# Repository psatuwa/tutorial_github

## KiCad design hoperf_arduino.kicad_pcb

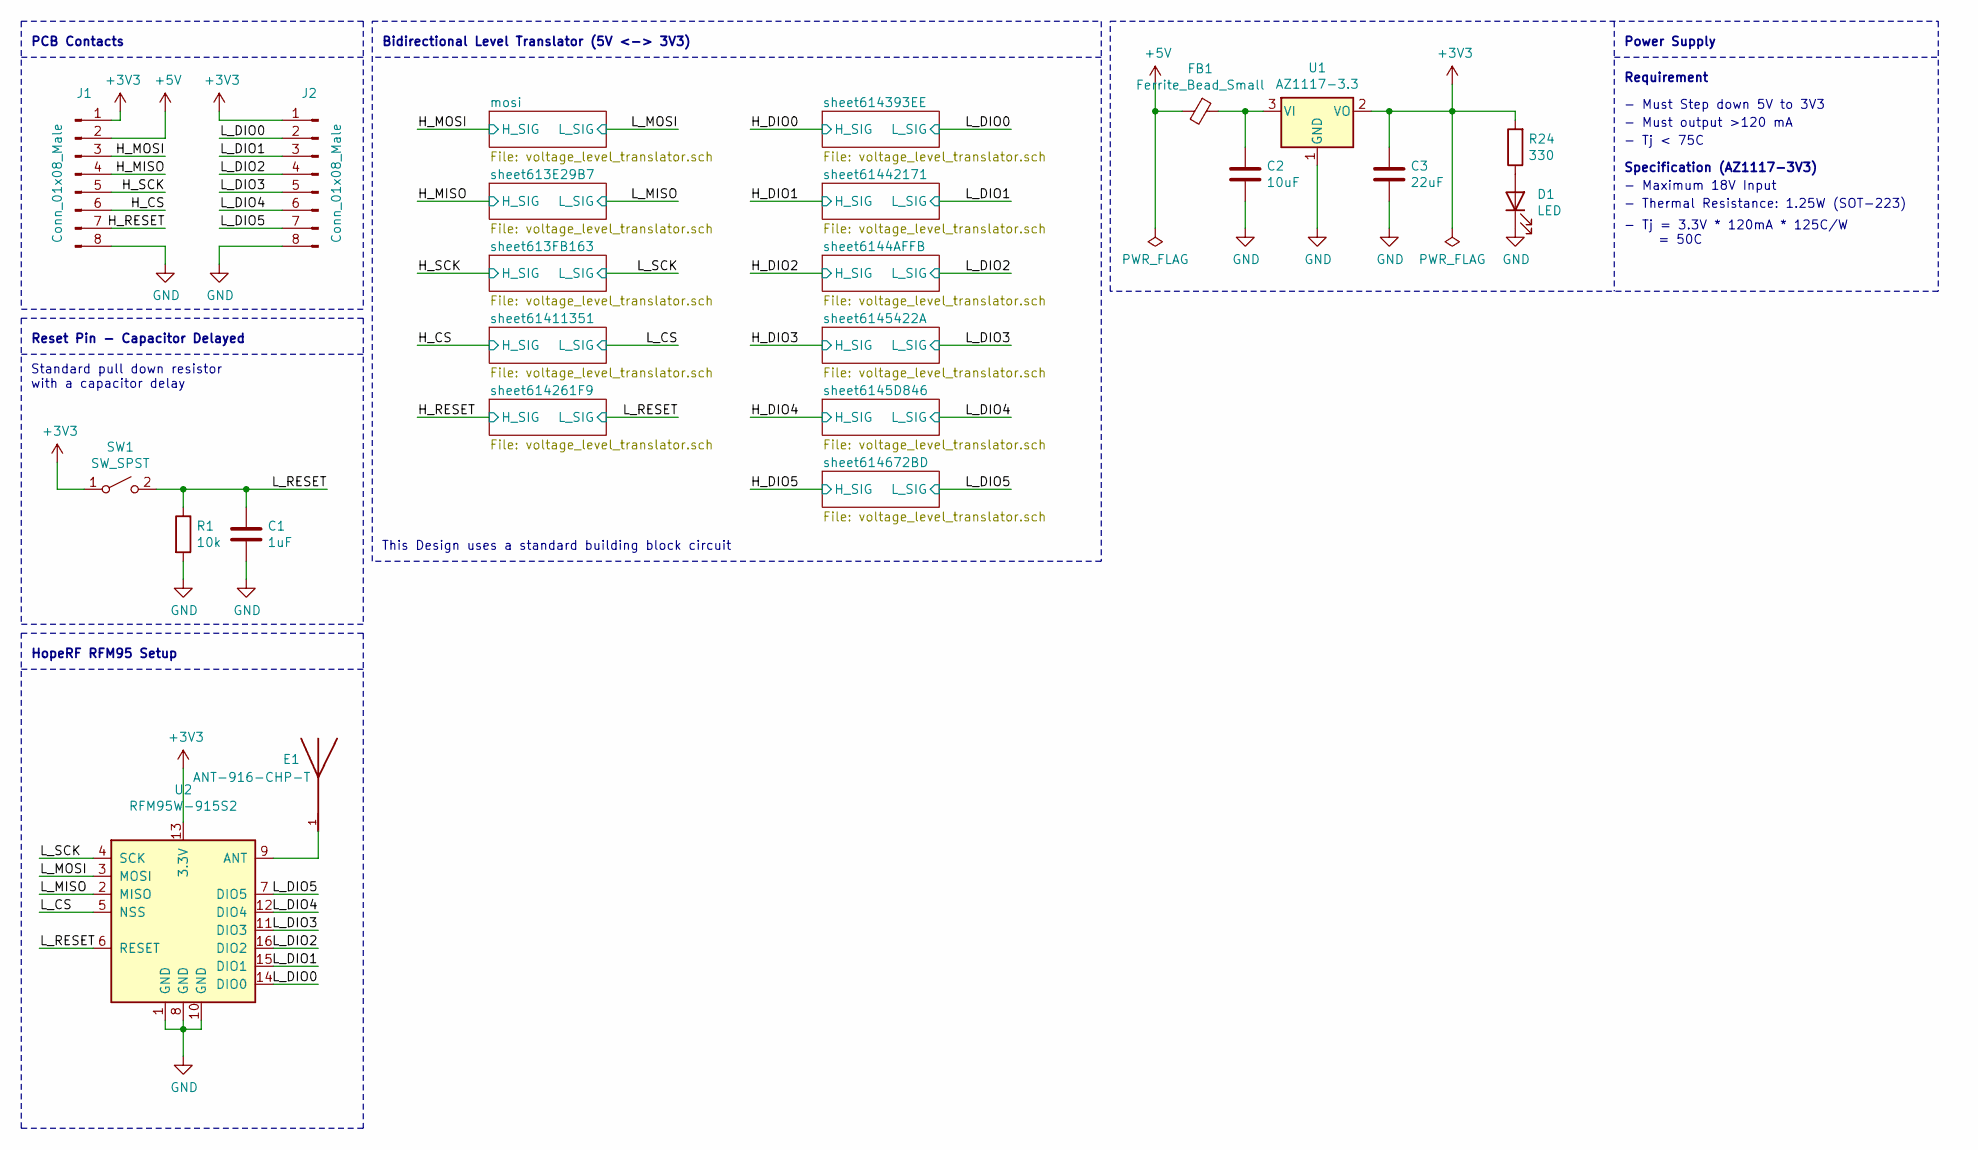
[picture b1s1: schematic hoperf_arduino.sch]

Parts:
C1: 1uF
C2: 10uF
C3: 22uF
D1: LED
E1: ANT-916-CHP-T; PARTREV C
FB1: Ferrite_Bead_Small
J1, J2: Conn_01x08_Male
R1: 10k
R24: 330
SW1: SW_SPST
U1: AZ1117-3.3
U2: RFM95W-915S2

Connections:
+3V3: C3.1, J1.1, J2.1, R24.2, SW1.1 (A), U1.2 (VO), U2.13 (3.3V); also elsewhere on the board
+5V: FB1.2, J1.2; also elsewhere on the board
/H_CS: J1.6; also elsewhere on the board
/H_MISO: J1.4; also elsewhere on the board
/H_MOSI: J1.3; also elsewhere on the board
/H_RESET: J1.7; also elsewhere on the board
/H_SCK: J1.5; also elsewhere on the board
/L_CS: U2.5 (NSS); also elsewhere on the board
/L_DIO0: J2.2, U2.14 (DIO0); also elsewhere on the board
/L_DIO1: J2.3, U2.15 (DIO1); also elsewhere on the board
/L_DIO2: J2.4, U2.16 (DIO2); also elsewhere on the board
/L_DIO3: J2.5, U2.11 (DIO3); also elsewhere on the board
/L_DIO4: J2.6, U2.12 (DIO4); also elsewhere on the board
/L_DIO5: J2.7, U2.7 (DIO5); also elsewhere on the board
/L_MISO: U2.2 (MISO); also elsewhere on the board
/L_MOSI: U2.3 (MOSI); also elsewhere on the board
/L_RESET: C1.1, R1.1, SW1.2 (B), U2.6 (RESET); also elsewhere on the board
/L_SCK: U2.4 (SCK); also elsewhere on the board
GND: C1.2, C2.2, C3.2, D1.1 (K), J1.8, J2.8, R1.2, U1.1 (GND), U2.1 (GND), U2.8 (GND), U2.10 (GND)
unnamed: C2.1, FB1.1, U1.3 (VI)
unnamed: D1.2 (A), R24.1
unnamed: E1.1, U2.9 (ANT)

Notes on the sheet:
Power Supply
Requirement
- Must Step down 5V to 3V3
- Tj < 75C
- Must output >120 mA
Specification (AZ1117-3V3)
- Maximum 18V Input
- Thermal Resistance: 1.25W (SOT-223)
- Tj = 3.3V * 120mA * 125C/W = 50C
Bidirectional Level Translator (5V <-> 3V3)
PCB Contacts
Reset Pin - Capacitor Delayed
This Design uses a standard building block circuit
Standard pull down resistor with a capacitor delay
HopeRF RFM95 Setup

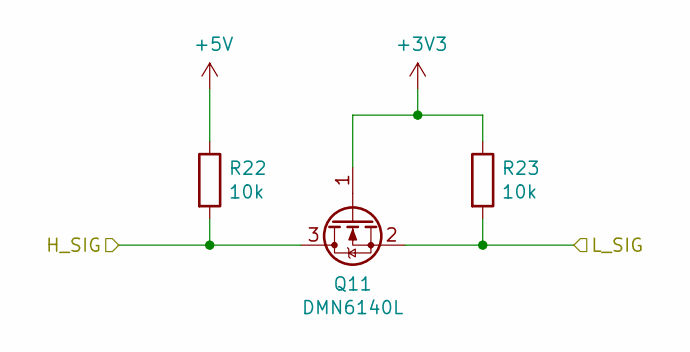
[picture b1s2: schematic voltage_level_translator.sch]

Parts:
Q1: DMN6140L
R2, R3: 10k

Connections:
+3V3: Q1.1 (G), R3.1; also elsewhere on the board
+5V: R2.1; also elsewhere on the board
/H_MOSI: Q1.3 (D), R2.2; also elsewhere on the board
/L_MOSI: Q1.2 (S), R3.2; also elsewhere on the board

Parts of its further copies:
Q2, Q3, Q4, Q5, Q6, Q7, Q8, Q9, Q10, Q11: DMN6140L
R4, R5, R6, R7, R8, R9, R10, R11, R12, R13, R14, R15, R16, R17, R18, R19, R20, R21, R22, R23: 10k

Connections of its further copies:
+3V3: Q2.1 (G), Q3.1 (G), Q4.1 (G), Q5.1 (G), Q6.1 (G), Q7.1 (G), Q8.1 (G), Q9.1 (G), Q10.1 (G), Q11.1 (G), R5.1, R7.1, R9.1, R11.1, R13.1, R15.1, R17.1, R19.1, R21.1, R23.1; also elsewhere on the board
+5V: R4.1, R6.1, R8.1, R10.1, R12.1, R14.1, R16.1, R18.1, R20.1, R22.1; also elsewhere on the board
/H_CS: Q4.3 (D), R8.2; also elsewhere on the board
/H_DIO0: Q6.3 (D), R12.2
/H_DIO1: Q7.3 (D), R14.2
/H_DIO2: Q8.3 (D), R16.2
/H_DIO3: Q9.3 (D), R18.2
/H_DIO4: Q10.3 (D), R20.2
/H_DIO5: Q11.3 (D), R22.2
/H_MISO: Q2.3 (D), R4.2; also elsewhere on the board
/H_RESET: Q5.3 (D), R10.2; also elsewhere on the board
/H_SCK: Q3.3 (D), R6.2; also elsewhere on the board
/L_CS: Q4.2 (S), R9.2; also elsewhere on the board
/L_DIO0: Q6.2 (S), R13.2; also elsewhere on the board
/L_DIO1: Q7.2 (S), R15.2; also elsewhere on the board
/L_DIO2: Q8.2 (S), R17.2; also elsewhere on the board
/L_DIO3: Q9.2 (S), R19.2; also elsewhere on the board
/L_DIO4: Q10.2 (S), R21.2; also elsewhere on the board
/L_DIO5: Q11.2 (S), R23.2; also elsewhere on the board
/L_MISO: Q2.2 (S), R5.2; also elsewhere on the board
/L_RESET: Q5.2 (S), R11.2; also elsewhere on the board
/L_SCK: Q3.2 (S), R7.2; also elsewhere on the board

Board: 2 copper layers, 46 parts (0 on the bottom side), 28 nets, no tracks yet.
